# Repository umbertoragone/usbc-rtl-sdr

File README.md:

# USB-C RTL-SDR mod
An adapter board to convert your RTL-SDR V3 or V4 USB-A (male) to USB-C (female). **Available for purchase on [Tindie](https://www.tindie.com/products/ragone/usb-c-rtl-sdr-v3v4-mod/) or [Lectronz](https://lectronz.com/products/usb-c-rtl-sdr-v3-v4-mod)!**

## Kicad files
If you want to open and modify the original project in Kicad 8 (>=8.0.7), you can find both the `.kicad_sch` and `.kicad_pcb` files in the `kicad` folder in this repository. I recommend you use the latest Kicad 8 version available for better compatibility.

## Gerber files
If you want to fabricate your own PCBs from a PCB manufacturer of your choice, you can go ahead and download the `Gerber-v1.x.zip` file from the `gerber` folder in this repository. Upload it or send it to the PCB fabrication house and select the following specifications (if not already filled out):
- **Layers**: 2
- **PCB Thickness**: 1.2 mm
- **PCB Color**: any (green is usually cheaper and faster to produce, but black also looks nice and might blend with the black outer case)
- **Surface finish**: HASL or ENIG (gold plating)
- **Outer Copper Weight**: 1 oz
- **Via Covering**: Tented
- **Mark on PCB**: Remove Mark (JLCPCB specific, now free of charge)
- **Castellated holes**: Yes

## BOM and assembly

Included in this repository is the HTML BOM (`ibom.html`) to help you in the assembly/soldering process after you received your PCBs. You can [access the Interactive HTML BOM here](https://umbertoragone.github.io/usbc-rtl-sdr/bom/ibom.html), without having to download the .html file. Also, here is the list of components you will have to source and solder yourself:

| Reference(s) | Value                   | Footprint         | LCSC Part #                                                   | Qty |
| ------------ | ----------------------- | ----------------- | ------------------------------------------------------------- | --- |
| R1, R2       | 5k1 1%                  | R_0402_1005Metric | [C25905](https://www.lcsc.com/product-detail/C25905.html)     | 2   |
| USB1         | USB_C_Receptacle_USB2.0 | TYPE-C-31-M-12    | [C2988369](https://www.lcsc.com/product-detail/C2988369.html) | 1   |

## How to perform the mod
1. Open the case of your RTL-SDR dongle by unscrewing the 2 screws on the USB A side.
2. Unscrew the locking nut on the SMA connector and make sure to remember the order they go in.
3. Carefully slide out the PCB from the metal housing.
4. Desolder the USB A connector from the board and clean the pads from any residual solder.
5. Position the USB C adapter board in place of the old USB A connector, like in the pictures, and tack it in place with some solder.
6. Solder all of the pins, including the two GND pads on the left and right sides of the USB C adapter board for mechanical strength.
7. (Optional) Clean the PCB and the soldered joints using 99.9% IPA (isopropyl alcohol).
8. Slide the board back in its metal housing, being careful of the thermal adhesive pad on the bottom of the PCB.
9. Lock the SMA connector in place and screw back the front panel of the metal housing (on the USB side).
10. Enjoy the USB C mod!

## Prebuilt option
If you're looking for an adapter board that's already assembled and ready to install on your RTL-SDR dongle, I offer a prebuilt option that's perfect for those who want a plug-and-play solution without the hassle of sourcing and assembling components. Each board is handcrafted and fully tested before shipping. **[Check it out on my Tindie store](https://www.tindie.com/products/ragone/usb-c-rtl-sdr-v3v4-mod/) or on [Lectronz](https://lectronz.com/products/usb-c-rtl-sdr-v3-v4-mod)**.

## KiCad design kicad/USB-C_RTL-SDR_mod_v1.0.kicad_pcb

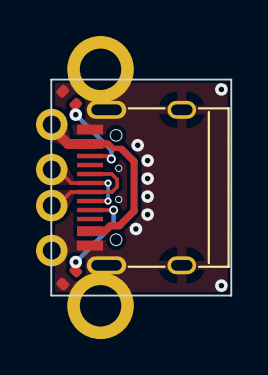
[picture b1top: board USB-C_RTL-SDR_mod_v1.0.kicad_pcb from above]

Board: 2 copper layers, 10.0 x 12.0 mm, 4 parts (0 on the bottom side), 6 nets.

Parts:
J1: USB_C_Receptacle_USB2.0; TYPE-C-31-M-12
J2: USB_A; USB_A_CONNFLY_DS1095-WNR0
R1, R2: 5k1; R_0402_1005Metric

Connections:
D+: J1.A6 (D+), J1.B6 (D+), J2.3 (D+)
D-: J1.A7 (D-), J1.B7 (D-), J2.2 (D-)
GND: J1.A1 (GND), J1.A12 (GND), J1.B1 (GND), J1.B12 (GND), J1.S1 (SHIELD), J2.4 (GND), J2.5 (Shield), R1.1, R2.1
unnamed: J1.A5 (CC1), R1.2
unnamed: J1.B5 (CC2), R2.2
VBUS: J1.A4 (VBUS), J1.A9 (VBUS), J1.B4 (VBUS), J1.B9 (VBUS), J2.1 (VBUS)

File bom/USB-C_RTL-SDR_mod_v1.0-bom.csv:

Comment,Designator,Footprint,LCSC
"USB_C_Receptacle_USB2.0","J1","USB_C:TYPE-C-31-M-12","C2988369"
"5k1","R1,R2","Resistor_SMD:R_0402_1005Metric","C25905"

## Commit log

2025-01-10 Add README.md with project details and manufacturing instructions
2025-01-10 Add .gitignore
2025-01-10 Update component properties in schematic: modify BOM inclusion and DNP status for several components, and add LCSC properties for new components.
2025-01-10 Add csv BOM and top position files for PCBA
2025-01-10 Upload new image
2026-02-14 Update README.md
    Add new image
2026-02-20 Fix screw count in RTL-SDR dongle mod instructions
    Corrected the number of screws to unscrew for opening the RTL-SDR dongle case.
